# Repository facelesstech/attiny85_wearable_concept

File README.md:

# attiny85_wearable_concept

A wearable platform built on a nato watch strap with a attiny85 and powered by a CR2032 coin cell. I used a tilt sensor as a button that turns each LED on in turn. 

Blog post - https://facelesstech.wordpress.com/2018/04/29/attiny-wearable/
Youtube - https://www.youtube.com/watch?v=YOjYC2ICE18

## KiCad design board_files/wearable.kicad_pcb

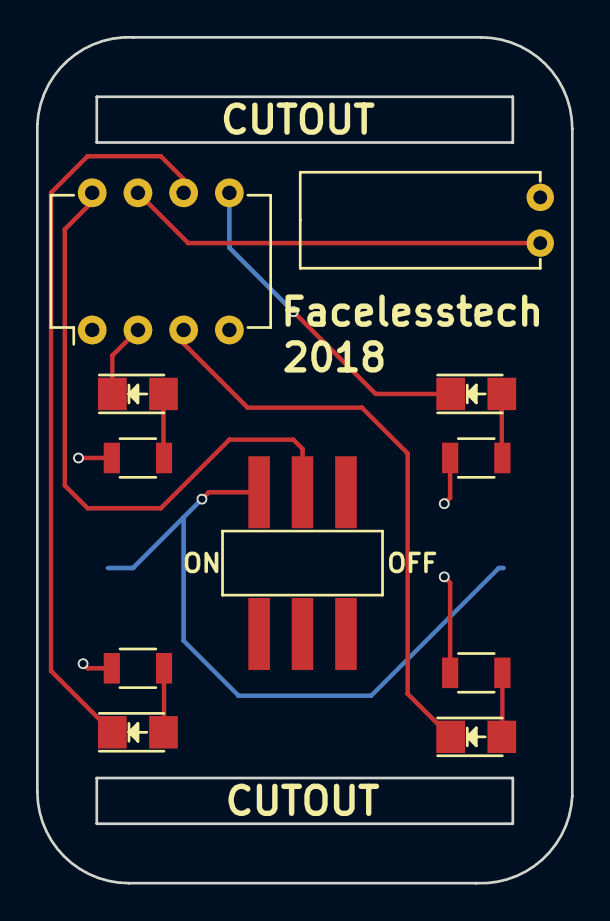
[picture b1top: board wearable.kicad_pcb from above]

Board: 2 copper layers, 29.7 x 47.0 mm, 12 parts (1 on the bottom side), 12 nets.

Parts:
BT1: Battery_Cell; Keystone_3034_1x20mm-CoinCell
D1, D2, D3, D4: LED; LED_1206
IC1: ATTINY85-P; DIP-8_W7.62mm
R1, R2, R3, R4: R; R_1206
SW1: SWITCH_INV; switch_6pin_smd_custom
U1: tilt_ball_custom; ball_tilt_custom

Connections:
unnamed: BT1.1, SW1.1
unnamed: BT1.2, IC1.4, R1.1, R2.1, R3.2, R4.1, U1.2
unnamed: D1.1, IC1.6
unnamed: D1.2, R1.2
unnamed: D2.1, IC1.3
unnamed: D2.2, R2.2
unnamed: D3.1, IC1.5
unnamed: D3.2, R4.2
unnamed: D4.1, IC1.2
unnamed: D4.2, R3.1
unnamed: IC1.7, U1.1
unnamed: IC1.8, SW1.2

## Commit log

2018-04-10 first upload
2018-04-11 board files for the attiny85 wearable
2018-04-12 moved files
2018-04-12 template for the wearable
2018-04-29 added links
